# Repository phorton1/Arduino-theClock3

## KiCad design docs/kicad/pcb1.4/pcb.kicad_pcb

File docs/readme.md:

# theClock3 - Accurate Electromagnetic Wooden Geared Clock

**Home** --
**[Design](design.md)** --
**[Plan](plan.md)** --
**[Wood](wood.md)** --
**[Coils](coils.md)** --
**[Electronics](electronics.md)** --
**[Firmware](firmware.md)** --
**[Assemble](assemble.md)** --
**[Build](build.md)** --
**[Tuning](tuning.md)** --
**[UI](ui.md)** --
**[Software](software.md)** --
**[Troubles](troubles.md)** --
**[Notes](notes.md)**

This clock uses wooden gears and a simple electromagnetically driven pendulum
with the goal of keeping accurate time.

It uses an an **electromagnet** and **permanent magnet** to provide pulses of energy
to the pendulum to keep it moving, an **angle sensor** to detect the position
of the pendulum, and a **magnetic spring** to to speed up, or slow down, the pendulum.

It uses a specially designed **cam driven pawl** mechanism to
reliably convert the motion of the pendulum in each direction
to the rotation of the **seconds wheel** and **gear train**.

It has a computer (an [**ESP32**](https://en.wikipedia.org/wiki/ESP32)) in it,
with a *Real Time Clock* (**RTC**) that is fairly accurate (to within about 1 second per day).
Furthermore the computer can connect to the internet to use Network Time Protocol
([**NTP**](https://en.wikipedia.org/wiki/Network_Time_Protocol))
to synchronize it's RTC within a few milliseconds of the *correct* international
**standard time**.

Roughly stated, the goal of this project is to produce a **wooden geared clock**
that will be accurate to within one second per day, or, when connected to the
internet, within one second at any given time over it's working lifetime.

This documentation is mostly geared towards makers who might like to build
one of these clocks. Though it is not a trivial task, this repository should
contain all of the information needed for you to build one.

## Documentation Outline

If you have received one of these clocks as a gift, please see the
**[Quick Start Guide](QuickStartGuide.pdf)** and the
**[User Interface](ui.md)** page for information on how to unpack,
setup, start, and use your clock.

The following pages of documentation are intended to as a *tutorial* for
a **maker** who is *building* a clock, and describes the step-by-step
process of constructing the clock and getting it running:

- **[Design](design.md)** - An overview of the **requirements** and **design** of the clock
- **[Plan](plan.md)** - A *plan* for **building** the clock, and the **BOM** (Bill of Materials)
- **[Wood](wood.md)** - **Laser Cutting** the wood and building the *Frame*, *Face*, and gluing the *Gears* together
- **[Coils](coils.md)** - **Winding** the *electromagnet coils*
- **[Electronics](electronics.md)** - Creating the custom **PCB** (printed circuit board), **Cables**, and **Connectors**
- **[Firmware](firmware.md)** - Compiling and installing the **Firmware** and doing a  **hardware test** of the electronics
- **[Assemble](assemble.md)** - Build the **sub-assemblies** of the clock, including **cutting the tubes** and assembling the **Gears, Pendulum,** and **Box**
- **[Build](build.md)** - **Final Build** of the clock, bringing all the *sub-assemblies* together into the finished *Clock*
- **[Tuning](tuning.md)** - Describes the process of getting the clock to **run accurately**

The remaining pages are considered **reference** materials for more
deeply understanding the clock and it's software:

- **[User Interface](ui.md)** - A detailed guide to the **User Interface** of the clock, including the *Buttons and LEDs*, and connecting to *WiFi* to use the *WebUI* and *Telnet*
- **[Software](software.md)** - A deeper look the **Software** of the clock, including an *Overview* of the functionality and a description of all of the *Parameters* for the clock
- **[Trouble Shooting](troubles.md)** - Some common potential **problems** and possible **solutions**
- **[Notes](notes.md)** - Other Notes and information about the clock

## Files Available in this repository

This clock was *designed* using the **Fusion 360** CAD program and
the [**KiCAD**](https://www.kicad.org/) schematic and PCB design program.
The main outputs from Fusion 360 are the **DXF Files** (drawings) used to laser
cut the wood, and the **STL Files** (3D models) used to 3D print the plastic parts.

The clock was *implemented* by using the **Lightburn** laser CNC machine
control program to cut the wood from the Fusion DXF files using my
[**20mm CNC machine**](https://github.com/phorton1/Arduino-esp32_cnc20mm),
and the **Prusa Slicer** and **OctoPrint** to slice the Fusion STL files and send
them to my **Prusa MK3S 3d printer** to make the plastic parts.

The PCB (printed circuit board) is almost it's own sub-project.
The outputs from *KiCad* include the basic **schematic**, and
the **Gerber** and **Excellon** files used to make the PCB.
The program [**FlatCAM**](https://bitbucket.org/jpcgt/flatcam/downloads/)
was used to generate the GCODE files from those files for running my
[**cnc3018**](https://github.com/phorton1/Arduino-esp32_cnc3018)
to **mill, epoxy coat, drill, and cut out** the PCB (printed circuit board.

The following sub-folders and their children can be found within this 'docs' folder

- [**fusion**](https://github.com/phorton1/Arduino-theClock3/tree/master/docs/fusion) -
   contains the main *Fusion 360* design **clock3.2.f3z**, as well as a few
   other files that support the design, including a CSV file containing parameters for
   the design, and a couple of **pyjoints** animations (which make use of the
   Fusion 360 [pyJoints Animation Plugin](https://github.com/phorton1/fusionAddIns-pyJoints)
   I wrote) that allowed me to visually test the design before implementing it.
  - [**dxf**](https://github.com/phorton1/Arduino-theClock3/tree/master/docs/fusion/dxf) -
    contains all of the DXF files used with **Lightburn** to laser cut the wooden parts
  - [**stl**](https://github.com/phorton1/Arduino-theClock3/tree/master/docs/fusion/stl) -
    contains STL files of all the plastic parts that I 3D printed
- [**kicad/pcb3.1**](https://github.com/phorton1/Arduino-theClock3/tree/master/docs/kicad/pcb3.1) -
  contains the **kiCAD** project, electronics schematics, and PCB design files
  - [**plot**](https://github.com/phorton1/Arduino-theClock3/tree/master/docs/kicad/pcb3.1/plot) -
    contains the Gerber/Excelon files output from kiCAD, along with the
    **FlatCAM** project used to produce the gcode files for milling, epoxy coating,
	drilling, and cutting out the PCB
    - [**gcode**](https://github.com/phorton1/Arduino-theClock3/tree/master/docs/kicad/pcb3.1/plot/gcode) -
	contains the final output gcode files for the PCB
- [**lightburn**](https://github.com/phorton1/Arduino-theClock3/tree/master/docs/lightburn) -
   contains **LBRN2** Lightburn files that contain all of
   the wooden parts to be laser cut, as well as individual files to cut
   the different thicknesses or types of wood
- [**prusa**](https://github.com/phorton1/Arduino-theClock3/tree/master/docs/prusa) -
   contains the Prusa **3mf** projects for the plastic parts I sliced
  - [**gcode**](https://github.com/phorton1/Arduino-theClock3/tree/master/docs/prusa/gcode) -
    contains the final output *Prusa MK3s* gcode files that I used to
    3D print the plastic parts

If you are a **maker** you do not necessarily need to mill your own PCB as I did.
You can implement this simple circuit using **perfboard**, or can use the
kicad files to (fairly quickly) design your own PCB to be created
from your favorite PCB supplier.   I simply choose to mill my own PCB's
because I don't live in a good place for shipments and am too impatient
to wait weeks (or months) to get a PCB.  You might be able to get one
from China in a few days, but it takes much longer for me where I live.

Another example is that you don't **need** to laser cut the wooden parts.
It should be possible to use a small CNC machine (3018) to mill the gears, and
either a slightly larger CNC machine to mill the frame parts, or they could
even be cut using templates and a jigsaw or scroll saw.

**HOW YOU BUILD IT IS UP TO YOU !!**

The reason I provide so much information in these pages (rather than just the bare minimum)
is specifically to allow some flexibility for your design/build workflow.
When I went to make my first wooden (and especially laser cut) clock, I could not find
any complete designs that I could build.  So I am hoping that the info here will
provide you both with the materials you need, and perhaps the impetus, to build
one of your own!

## Credits

This project directly relies upon the public open source Arduino development system,
the Espressif ESP32 online documentation and additions to the Arduino IDE, as
well as a number open source Arduino libraries

I would like to thank the countless individuals who have contributed to making these
development tools, source codes, and documentation available for free public use, including,
but not limited to:

- [KiCad](https://www.kicad.org/)
- [FlatCAM](https://bitbucket.org/jpcgt/flatcam/downloads/) by **Juan Pablo Caram**
- [Arduino IDE and Libraries](https://www.arduino.cc/)
- [Espressif Systems](https://www.espressif.com/en/products/socs/esp32)
- [Adafruit NeoPixel Library](https://github.com/adafruit/Adafruit_NeoPixel)
- [AS5600 Library](https://github.com/RobTillaart/AS5600) by **Rob Tillaart**

## License

This program, project, and repository is free software: you can redistribute it and/or modify
it under the terms of the GNU General Public License Version 3 as published by
the Free Software Foundation.

These materials are distributed in the hope that they will be useful,
but WITHOUT ANY WARRANTY; without even the implied warranty of
MERCHANTABILITY or FITNESS FOR ANY PARTICULAR PURPOSE.  See the
GNU General Public License for more details.

Please see [LICENSE.TXT](../LICENSE.TXT) for more information.

## Please Also See

This project directly or indirectly brings together a number of other projects of mine.
It supersedes my previous clock projects, [**theClocks 1&2**](https://github.com/phorton1/Arduino-theClock),
and makes direct use of my
[**MyIOT**](https://github.com/phorton1/Arduino-libraries-myIOT)
("my internet of things*) repository, which provides a generalized approach to building parameter
driven ESP32 devices that include a Web UI, as the basis for the software.

Another project that also make user of the *myIOT* repository is the
[**Bilge Alarm**](https://github.com/phorton1/Arduino-bilgeAlarm)
that I built for my boat.

The PCB (printed circuit board) was **milled** using the
[**cnc3018**](https://github.com/phorton1/Arduino-esp32_cnc3018) CNC
machine that I built, and the wooden parts were cut using the laser configuration of the larger
[**20mm CNC machine**](https://github.com/phorton1/Arduino-esp32_cnc20mm) that I subsequently built.
Both of those projects depend on my port of the
[**FluidNC**](https://github.com/phorton1/Arduino-libraries-FluidNC)
ESP32 based CNC controller firmware, and include my
[**FluidNC UI**](https://github.com/phorton1/Arduino-libraries-FluidNC_UI)
(touchscreen user interface) and
[**other extensions**](https://github.com/phorton1/Arduino-libraries-FluidNC_Extensions)
that I added to the FluidNC library.

There is also a quick and dirty
[**Coil Winding Machine**](https://github.com/phorton1/Arduino-CoilWindingMachine)
project repository for the machine I made to wind the coils for these clocks and
a [Fusion 360 Plugin](https://github.com/phorton1/fusionAddIns-pyJoints)
that I created which allowed me to do animations of the clock to visually see how the
mechanism might work before actually building it.

I hope you will take a few minutes to check out some of these other pages too!!

**Next:** A [**Design Overview**](design.md) of the clock ...

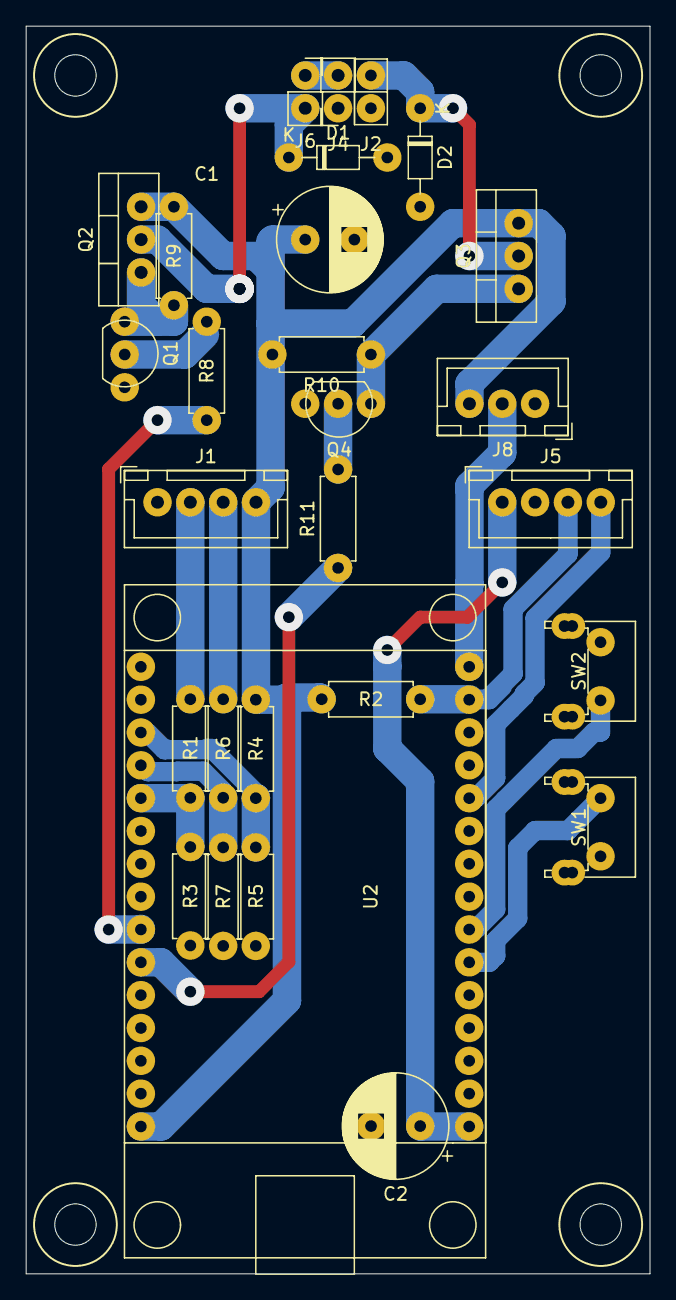
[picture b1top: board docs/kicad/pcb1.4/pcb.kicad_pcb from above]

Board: 2 copper layers, 48.3 x 96.5 mm, 28 parts (0 on the bottom side), 22 nets.

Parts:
C1: 330uf; CP_my100uf
C2: 100 uf; CP_my100uf
D1, D2: 1N4741; myZenerDiode
J1: power; myJSTx04
J2: coil3; myPinSocket_1x02
J4: coil1; myPinSocket_1x02
J5: Sensor; myJSTx04
J6: coil2; myPinSocket_1x02
J8: leds; myJSTx03
Q1, Q4: BC548; myTransistor
Q2, Q3: IRF9540N; myThreeLegged
R1, R2, R3, R4, R5, R6, R7, R8, R9, R10, R11: 10K; myResistor
SW1, SW2: SW; myButtonAngled
U2: ESP32_DEV_0; myESP32DEV0

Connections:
+3V3: C2.1, J5.1, U2.30
+5V: C1.1, J1.4, J8.3, Q2.3, Q3.3, R2.1, R4.2, R9.2, R10.2, U2.1
COIL1+: D1.1, J6.2, Q2.2
COIL2+: D2.1, J2.2, Q3.2
GND: C1.2, C2.2, D1.2, D2.2, J1.1, J2.1, J4.1, J5.2, J8.1, Q1.3, Q4.3, R3.2, R5.2, R7.2, SW1.2, SW2.1, U2.2, U2.29
LEDS: J8.2, U2.16
unnamed: J4.2, J6.1
unnamed: Q1.1, Q2.1, R9.1
unnamed: Q1.2, R8.2
unnamed: Q3.1, Q4.1, R10.1
unnamed: Q4.2, R11.2
PWM1: R8.1, U2.7
PWM2: R11.1, U2.6
S5V: R4.1, R5.1, U2.13
SBAT: R1.1, R3.1, U2.11
SBUS: R6.1, R7.1, U2.12
SCL: J5.3, R2.2, U2.17
SDA: J5.4, U2.20
SW1: SW1.1, U2.25
SW2: SW2.2, U2.24
VBAT: J1.2, R1.2
VBUS: J1.3, R6.2

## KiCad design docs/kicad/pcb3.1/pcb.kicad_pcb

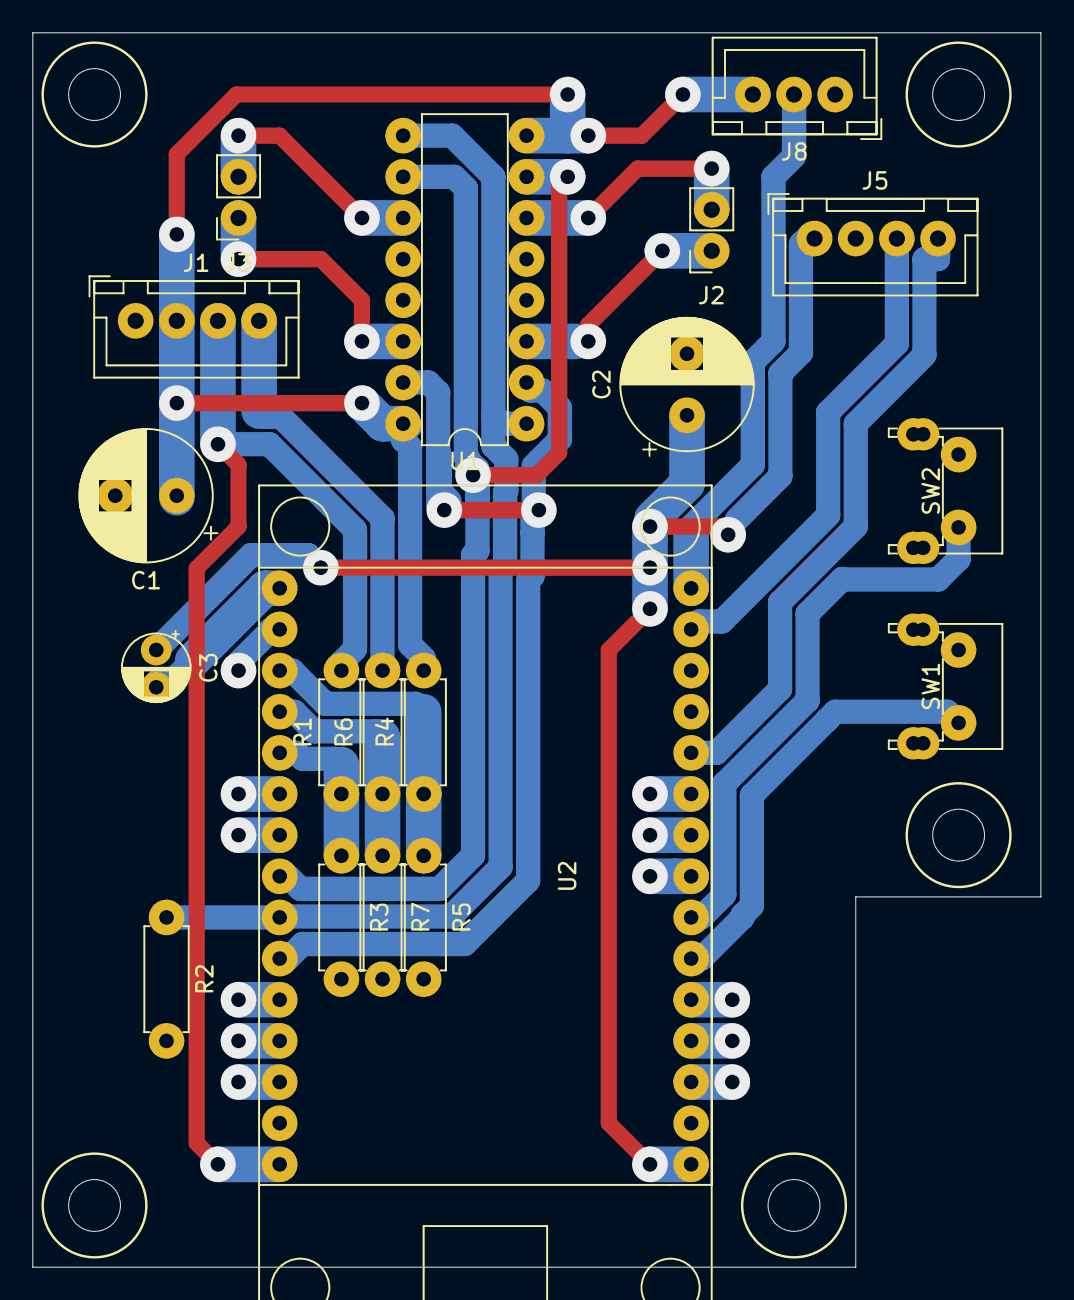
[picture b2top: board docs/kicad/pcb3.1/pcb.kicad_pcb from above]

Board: 2 copper layers, 62.2 x 76.2 mm, 19 parts (0 on the bottom side), 21 nets.

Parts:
C1: 100uf; CP_my100uf
C2: 470uf; CP_my100uf
C3: 10uf; CP_my10uf
J1: power; myJSTx04
J2: coil1; myPinSocket_1x02
J3: coil2; myPinSocket_1x02
J5: Sensor; myJSTx04
J8: leds; myJSTx03
R1, R2, R3, R4, R5, R6, R7: 10K; myResistor
SW1, SW2: SW; myButtonAngled
U1: L293D; myDip16
U2: ESP32_DEV_0; myESP32DEV0

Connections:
+3V3: C2.1, C3.1, J5.1, U2.30
+5V: C1.1, J1.2, J8.3, R4.2, U1.8, U1.16
EN: R2.1, U1.1, U1.9, U2.7
GND: C1.2, C2.2, J1.1, J5.2, J8.1, R2.2, R3.2, R5.2, R7.2, SW1.1, SW2.1, U1.4, U1.5, U1.12, U1.13, U2.2, U2.29
I1: U1.2, U1.15, U2.6
I2: U1.7, U1.10, U2.8
LEDS: J8.2, U2.16
unnamed: C3.2, U2.15
OA1: J2.1, U1.3
OA2: J2.2, U1.6
OB1: J3.1, U1.14
OB2: J3.2, U1.11
S5V: R4.1, R5.1, U2.13
SBAT: R6.1, R7.1, U2.12
SBUS: R1.1, R3.1, U2.11
SCL: J5.3, U2.17
SDA: J5.4, U2.20
SW1: SW1.2, U2.25
SW2: SW2.2, U2.24
VBAT: J1.4, R6.2
VBUS: J1.3, R1.2, U2.1

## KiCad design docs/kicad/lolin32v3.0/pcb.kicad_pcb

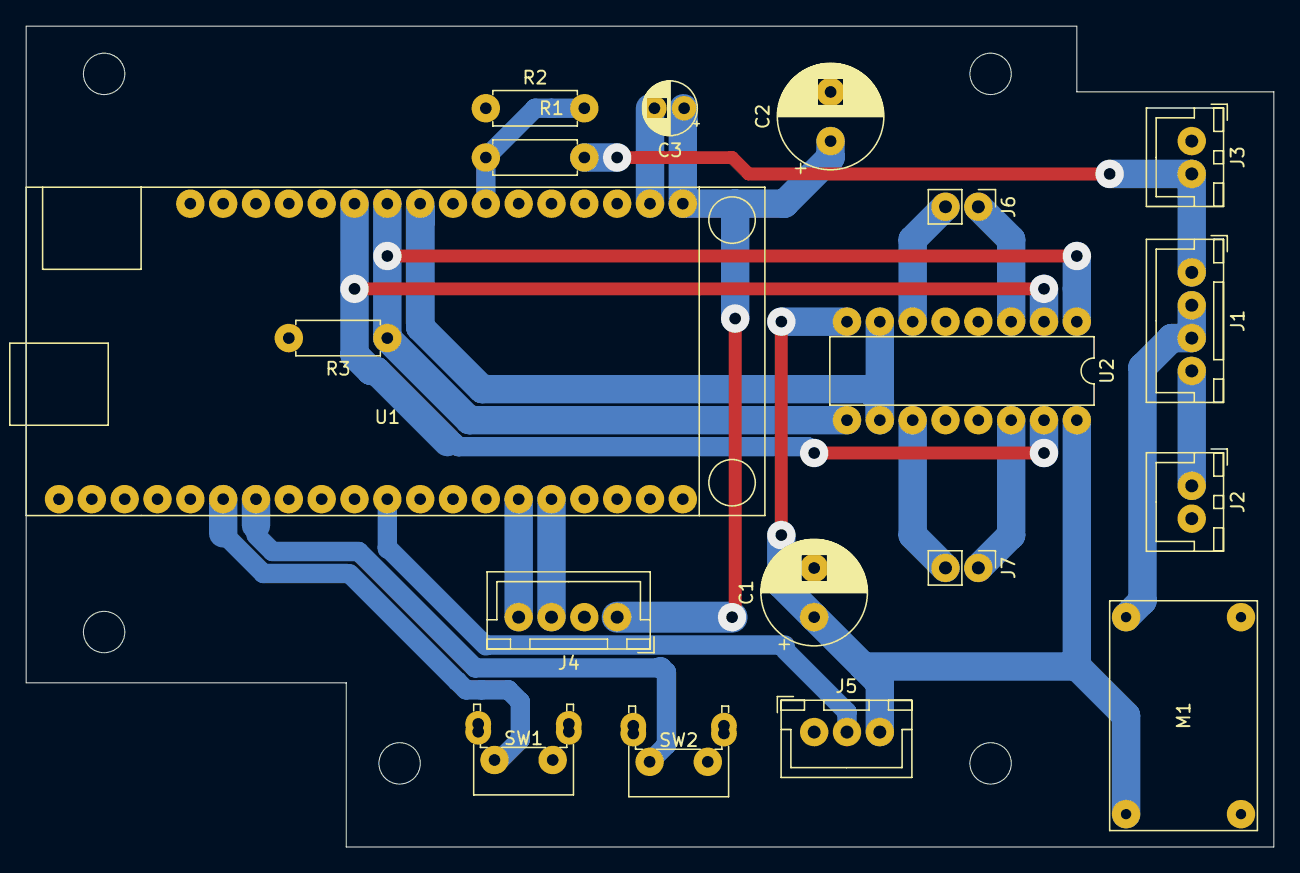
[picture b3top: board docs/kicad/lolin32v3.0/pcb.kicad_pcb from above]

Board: 2 copper layers, 96.5 x 63.5 mm, 18 parts (0 on the bottom side), 20 nets.

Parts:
C1, C2: 100uf; CP_my100uf
C3: 10uf; CP_my10uf
J1: power; myJSTx04
J2: battery; myJSTx02
J3: BATT; myJSTx02
J4: Sens1; myJSTx04
J5: leds; myJSTx03
J6: coil1; myPinHeader_1x02
J7: coil2; myPinHeader_1x02
M1: BUCK01; myMini360BuckConverter
R1, R2: 47K; myResistor
R3: 10K; myResistor
SW1, SW2: SW; right_angle_button
U1: LOLIN32; myLolin32
U2: L293D; myDip16

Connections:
+3V3: C2.1, C3.1, J4.1, U1.21
+5V: C1.1, J5.3, M1.3, U2.8, U2.16
BAT+: J1.1, J3.2, R1.2
BAT_SENSE: R1.1, R2.2, U1.27
EN: R3.1, U1.30, U2.1, U2.9
GND: C1.2, C2.2, J2.2, J3.1, J4.2, J5.1, M1.1, M1.2, R2.1, R3.2, SW1.1, SW2.1, U1.3, U1.13, U1.14, U1.20, U1.36, U2.4, U2.5, U2.12, U2.13
I1: U1.31, U2.2, U2.15
I2: U1.29, U2.7, U2.10
LEDS: J5.2, U1.11
unnamed: C3.2, U1.22
unnamed: J1.2, J1.3, M1.4
unnamed: J1.4, J2.1
OA1: J6.1, U2.3
OA2: J6.2, U2.6
OB1: J7.1, U2.14
OB2: J7.2, U2.11
SCL: J4.3, U1.16
SDA: J4.4, U1.15
SW1: SW1.2, U1.6
SW2: SW2.2, U1.7

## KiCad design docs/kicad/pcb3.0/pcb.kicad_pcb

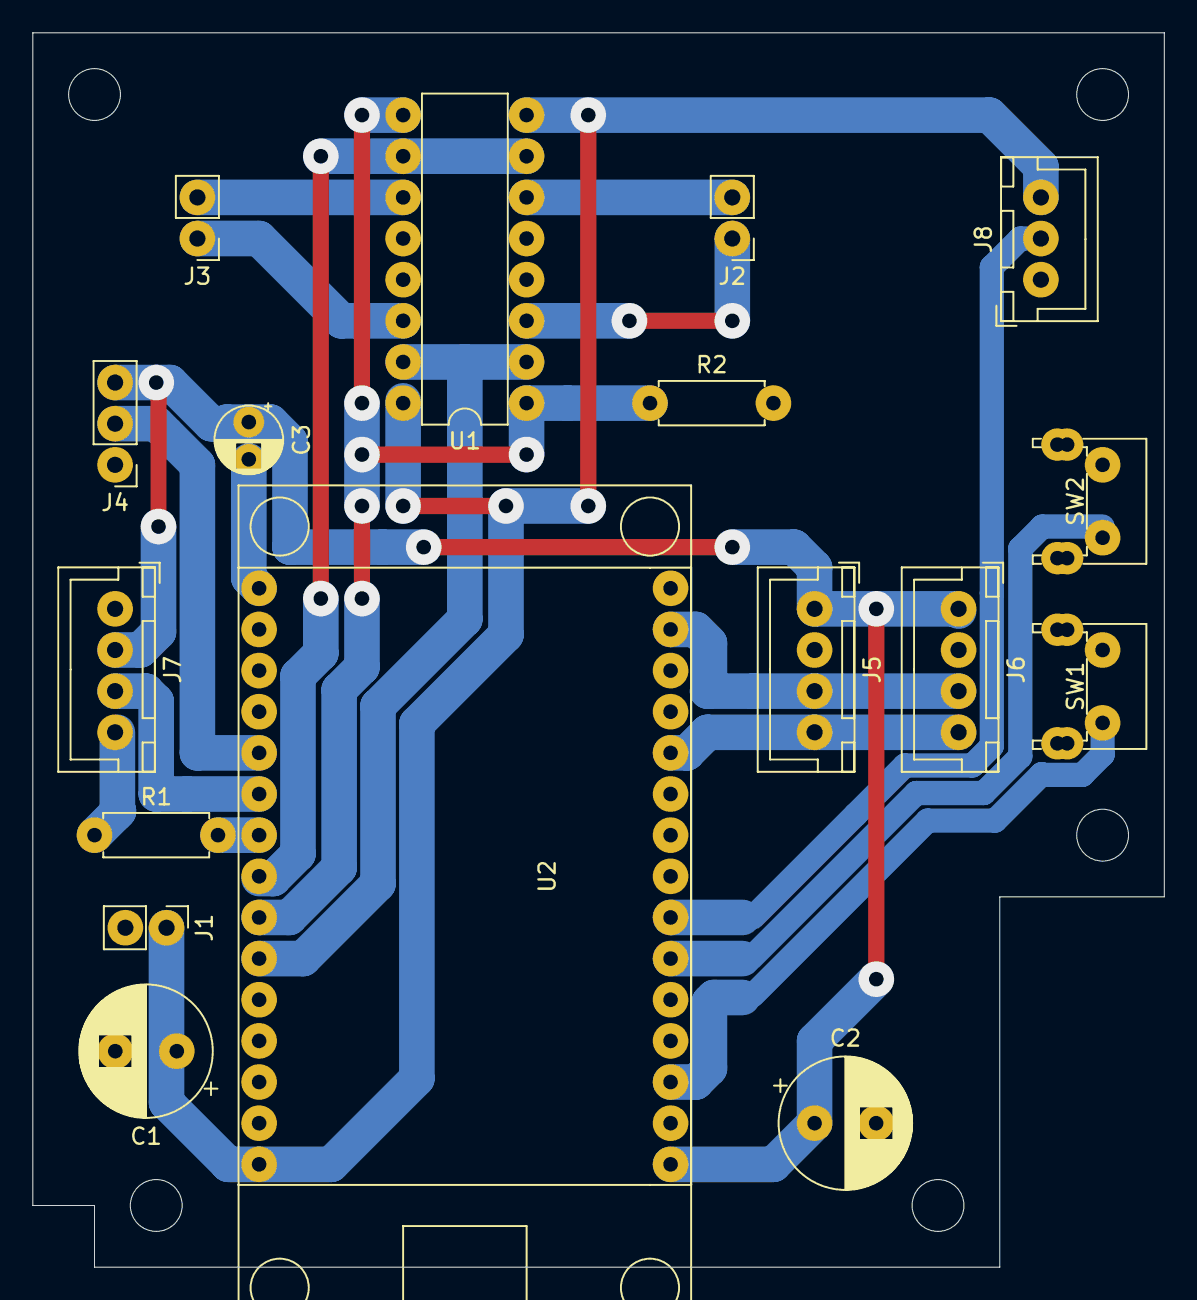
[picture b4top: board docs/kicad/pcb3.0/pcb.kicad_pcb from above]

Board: 2 copper layers, 69.8 x 76.2 mm, 17 parts (0 on the bottom side), 20 nets.

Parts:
C1, C2: 100uf; CP_my100uf
C3: 10uf; CP_my10uf
J1: power; myPinHeader_1x02
J2: coil1; myPinHeader_1x02
J3: coil2; myPinHeader_1x02
J4: hall; myPinHeader_1x03
J5: Sens1; myJSTx04
J6: Sens2; myJSTx04
J7: Opto; myJSTx04
J8: leds; myJSTx03
R1: 220; myResistor
R2: 10K; myResistor
SW1, SW2: SW; right_angle_button
U1: L293D; myDip16
U2: ESP32_DEV_0; myESP32DEV0

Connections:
+3V3: C2.1, C3.1, J4.3, J5.1, J6.1, J7.2, U2.30
+5V: C1.1, J1.1, J8.3, U1.8, U1.16, U2.1
EN: R2.1, U1.1, U1.9, U2.7
GND: C1.2, C2.2, J1.2, J4.1, J5.2, J6.2, J7.1, J8.1, R2.2, SW1.1, SW2.1, U1.4, U1.5, U1.12, U1.13, U2.2, U2.29
I1: U1.2, U1.15, U2.6
I2: U1.7, U1.10, U2.8
LEDS: J8.2, U2.24
unnamed: C3.2, U2.15
unnamed: J7.4, R1.1
OA1: J2.1, U1.3
OA2: J2.2, U1.6
OB1: J3.1, U1.14
OB2: J3.2, U1.11
SCK: J7.3, U2.10
SCL: J5.3, J6.3, U2.17
SDA: J5.4, J6.4, U2.20
SDIO: R1.2, U2.9
SW1: SW1.2, U2.28
SW2: SW2.2, U2.25
hall: J4.2, U2.11

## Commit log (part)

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2023-03-16 copy files from theClock/pcb1.1, rename, and check in
2023-03-17 initial v3 circuit board, pin assigments in code TODO: code in general
2023-03-21 add 'data' directory
2023-03-21 correct 5165 to 5155!! bearing
2023-03-21 build wood and plastic
2023-03-21 revert to 5165 bearing
2023-03-22 changed to 2.6 screw3_tight_wood, updated drawings, got rid of most lightburn for eas of maintenance
2023-03-25 change 3.1 to 3.0 and generate flatcam stuff
2023-03-27 build thinner v3.0
2023-03-27 begin work on code for v3
2023-03-30 initial commit of swing degree PID controller
2023-03-30 fixed magnet sixe in pendulum
2023-03-30 various minor physical changes
2023-03-30 added alternate arm2 and pawl2
2023-03-30 remove HALL, cleanup, initial STATS
2023-03-31 initial working checkin (BEFORE SOLVING BASIC FREQUENCY ISSUE)
2023-03-31 BETTER ALGORITHM - KEEPS TIME AND ANGLE PRETTY WELL!
2023-04-02 constants and colors only
2023-04-02 blah blah blah
2023-04-03 sanity checkin - trying to run down AS5600 error - changed startup logic, parameterized much additional stuff, still just skips bad as5600 readings ... sigh
2023-04-06 change sync message display (only)
2023-04-10 2ND PID CONTROLLER - NEW ALGORITHM - NO "PULLS" - WORKS GOOD
2023-04-10 refine constants; design and print magnet_holder; prep for startClockSynchronized
2023-04-11 rework LEDS in prep for startClockSynchronized()
2023-04-12 fighting with detailed synchronization and readAngle() vs showPixels()
2023-04-13 added PIXEL_MODE and LED_BRIGHTNESS; had problem with loop() static uint32_t!!! messed with IRAM_ATTR; solution? --> made many vars volatile;
2023-04-14 move long comments from code to readme
2023-04-15 FOUND THE MEMORY BUG! - got rid of volatiles - fixed timeAddMS *secs-- and onSyncRTC sign problem - made clearStats() really start over
2023-04-15 defaults, LOG, and wifi_off BLUE_LED only
2023-04-16 minor changes (prep for big myIOT rewrite?)
2023-04-16 fixed compiler warnings and one bug with this_p = cur_cycle
2023-04-16 change cur_cycle to int32_t; indentation and comments
2023-04-16 factor code - prep for doButtons()
2023-04-16 implement buttons; test default values;
2023-04-17 added Wifi checks to onSyncRTC
2023-04-17 implemented PIXEL_TIME_MODE
2023-04-17 fixed PIXEL_MODE_TIME time intervals and added m_start_sync==MY_LED_WHITE
2023-04-18 added button support for PIXEL_MODE_TIME and changed colors again
2023-04-19 CREATED V1.3 as clock 1.1 with V3 sensor and software
2023-04-21 turn off V1.3 define
2023-04-21 added adjustable ranges for DIAG _cycle_range and _error_range pixels
2023-04-22 separated V1 PINS from BEHAVIOR so I could build LOLIN32 with correct pins, but V1 behavior
2023-04-22 test change for github auth
2023-04-22 nuther github auth test
2023-04-23 LOLIN32 pcb - changed voltage divider resistors
2023-04-23 Added WITH_VOLT_CHECK define, turns on PIN_VOLT_CHECK and parameters VOLT_VALUE, VOLT_INTERVAL, and VOLT_CALIB
2023-04-23 Retry initing AS5600 a few times if it fails
2023-04-23 made ID_RUNNING memory only and changed START_SYNC to a real boolean parameter
2023-04-23 made global as5600_connected and changed getAS5600Angle() to return zero_angle if not connected and always update_direction
2023-04-23 basic implementation (and stats) for LOW_POWER_MODE
2023-04-23 moved REVERSE_PIXELS up - checked in with LOLIN32 test circuit defines
2023-04-25 added lolin32 pcb & step; started 5VUPS schematic
2023-04-25 made V1.3 defaults official - checked in as V3.1
2023-04-28 added 3.1 pcb, dxfs, prepare to build
2023-05-01 update constants. clear ang_error on sync done
2023-05-01 rebuild normal ESP32_dev0
2023-05-03 yet another tuning of clock3
2023-05-08 latest constants for 3.1 clock
2023-05-09 finish wood build
2023-05-12 diddle params again, add BOM, and washer_x8.gcode
2023-05-21 various extra files generated while building 3 x v3.2 clocks
2023-05-21 upgrade to version 3.2 and default correct clock3 pins
2023-05-27 re-implemented START_SYNC to use ms before 0 to start (was ms after 59 previously)
2023-05-27 temporary 'alternate arms' build
2023-05-31 comment only
2023-06-01 FINALISH BUILD THREE CLOCKS - lots of changes changed startAS5600 to flash all LEDs upon failure, and for CLOCK_STATE led to flash red in that case. changed setZeroAngle() to retry upto 5 times 45 to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
2023-06-07 updated to new captive.html
2023-06-07 changed medium press to CYAN for better distinction
2023-06-08 added QuickStartGuide.docx, removed versioned output files
2023-06-09 2023-06-08 Shipped Quick Start Guide
2023-06-09 push to test videos
2023-06-12 spell_checked readme.md
2023-06-14 documentation WIP - add Build and Firmware pages; cleanup lightburn and prusa materials
2023-06-16 documentation WIP - changed "rider" to "bridge" and "frame main" to "frame middle"
2023-06-16 Docs - add link(s) to new Arduino-CoilWindingMachine repository
2023-06-17 Docs - renamed fusion tool parts to "Left" and "Right", finished "Coils" page and renamed "Plastic" to "Box"
2023-06-19 documentation WIP thru "software.md"
2023-06-20 documentation WIP - sorta finished other.md
2023-06-21 updated pcb3.3 (no plots, flatcam, or gcode)
2023-06-21 changed v3.3 defaults for SERIES coils with mosfet board. Implemented negative start_delay AFTER zero. Set default RESSTART_MIILLIS=0
2023-06-24 Rework PCB3.3, import it into fusion, more documentation WIP
2023-06-24 fixed bad bridge DXF file
2023-06-24 fusion selection sets for USB mount and quick UPS mount for box
2023-06-25 got rid of fusion internal USB_UPS, added external USB_UPS box
2023-06-25 fusion usb_usp forgot an extrusion
2023-06-26 update documentation to new pcb3.3 MOSFET PCB
2023-06-26 docs electronics continued ..
2023-06-27 document WIP - assembly.md
2023-06-28 updated/added pics, added YouTube WindingCoils video
2023-06-29 docs - added Ticking YouTube video, Build (ticking) Animation, and more images to Other page
2023-06-29 doc - added assem-top_tube.gif, spell checked thru assem
2023-07-02 docs - added FinalBuildMontage youtube video, renamed pages and images
2023-07-02 github does not like <style> elements in MD files
2023-07-02 doc typos and minor corrections
2023-07-04 started docs Tuning WIP
2023-07-04 docs - Finished "Tuning" page
2023-07-04 docs - shrink build-gears.gif image
2023-07-05 cleaned up PARAM DEFINES; added PARAMS to ui.md (WIP); updated javascript to use Tooltips
2023-07-06 doc WIP - ui.md LEDs mostly
2023-07-06 test tables on github
2023-07-06 docs ui fix startup LED image
2023-07-06 docs misc
2023-07-06 Unified section number schemes ## A,B,C ... and ### 1,2,3....
2023-07-07 docs - added software-connectWebUI and anchor links
2023-07-08 doc WIP - UI continued
2023-07-08 docs - rename software to firmware and break software.md out of ui.md
2023-07-08 docs - fix broken links
2023-07-08 docs - start Notes page
2023-07-08 docs-notes - added optional 2nd USB connector and UPS Power Supply
2023-07-08 docs - finished notes page
2023-07-09 docs - initial public push
2023-07-09 doc - typos
2023-07-10 doc typos
2023-07-10 doc - make USB_UPS box bigger
2023-07-10 cleaned up LOW_POWER stats
2023-07-10 changed DEFAULT_RUNNING_ERROR to 4 degrees, added PID comments for v3.2 built #3/3, fix sminor doc typos
2023-09-13 update preferences.txt to new port
2023-10-20 comments only
2023-11-02 nuther try
2023-11-02 one more try
2023-11-02 fix broken links across all repos with introduction of base-apps-gitUI::repoDocs.pm
2024-01-07 IMPLEMENT CLOCK 1.4 with new PCB and 2nd Spring Coil - clean up defines, etc.
2024-01-10 added CLEAR_ERRORS command/id/button etc
2024-02-03 refine clock 1.4 to USE_LEFT angle for m_angle_pid for consistent spring behavior
2024-02-11 changed 1.04 to simple ALL-ON or ALL-OFF spring algorithm with new tuning
2024-03-01 rebuild clock3
2024-03-01 remove data folder for change to submodule
2024-03-01 made 'data' directory into submodule of myIOT/data_master
2024-07-19 submodule(data) auto_commit(9478759f) addl iotCommon.js submodule changes for control and disabled_classses
2024-09-08 comments only RETUNED PID for clock3.3
2024-09-21 submodule(data) auto_commit(83767cf1) Added a Widget tab to the main myIOT webpage; added jqplot CSS and JS files; wrote iotPlot.js prototype of charting within a "widget" - see fridgeController chec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
2024-09-22 submodule(data) auto_commit(e76456cf) iotPlot.js - minor change to Fix Zooming; otherwise "comments only"
2024-09-25 refined myIOT plotter with LEGENDS and using device specific PLOT_TYPES if available; theClock3 implementation of PLOT_CYCLES and PLOT_WAVES
2024-09-25 submodule(data) auto_commit(331f60b7) refined myIOT plotter with LEGENDS and using device specific PLOT_TYPES if available; theClock3 implementation of PLOT_CYCLES and PLOT_WAVES
2024-09-25 submodule(data) auto_commit(18ec6f60) iotPlot.js - missing ctx.lineWidth = 1; for plot itself
2024-09-26 submodule(data) auto_commit(68039dc2) prep for bilgeAlarm bar chart widget - reworked myIOTDataLog to send records from back of file until dt stamp is met, which required myIOTWebServer to use HTTP 1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
2024-09-29 submodule(data) auto_commit(416ed000) added prototype bilgeAlarm jqPlot Widget using added "alt_data_format" and custom chart_header and chart_data code in onCustomLink(). modified myIOT/data index.h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
2024-10-01 submodule(data) auto_commit(2407a228) added global DEGREE_TYPE and VALUE_STYLE_TEMPERATURE, supprted in webUI, dataLog, and Charts
2024-10-07 submodule(data) auto_commit(f3e2065d) reduce size of WS status fields in index.html
2024-10-10 submodule(data) auto_commit(b622c3ba) Use regular javascript alert instead of myAlert and hide progress on upload_error
2024-10-19 submodule(data) auto_commit(c0e7ba5a) add better resizing to iotChart.js
2024-10-25 submodule(data) auto_commit(fdbad871) fix myIOTServer with new chart stuff (pass uuids, caching, etc)
2024-11-07 refork NMEA2000 libraries; cleanup FluidNC_Extensions::mesh.cpp() and cnc3018.h CNC_MACHINE, UI_WITH_MESH and USE_LARGE Mesh defines and compile messages - turning off default definition of UI_WITH_M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
2025-12-15 submodule(data) auto_commit(b649fc3a) iotChart.js - added scheme for setting device specific series colors
2025-12-18 submodule(data) auto_commit(1adaeb45) reworked iotChart.js incremental update scheme starting with Arduino-boat-drainPump
2025-12-18 submodule(data) auto_commit(1efc7b72) rework iotChart.js::determineNumberTicks() starting with drain_pump
2025-12-18 submodule(data) auto_commit(78894e93) change onChartResize() to use create_chart() instead of built in jqplot.replot()
2025-12-18 submodule(data) auto_commit(40916b0c) separate iotChart.js doChart() as init only method from onXXX() UI methods - yet another rework of iotChart.js and myIOTDataLog starting with fridgeController
2025-12-18 submodule(data) auto_commit(a4e2ed81) change chart.html and iotChart.js to use and remove style "degree_hidden" for devices that chart things with degrees
2025-12-18 submodule(data) auto_commit(a9754dbc) fixed renamed control _degree_type
2025-12-18 submodule(data) auto_commit(03555741) fix malformed chart.html <select id='_chart_period'> text
2025-12-19 submodule(data) auto_commit(253976a9) more changes to iotChart.js starting with tempController so at least refresh works *well* if no zooming involved
2025-12-19 commit parents
2025-12-20 submodule(data) auto_commit(eccd1fcc) iotChart.js - added save/restore of series visibility and refactored code
2025-12-31 submodule(data) auto_commit(2a8db875) add degree_type to myIOT chart_header for use in initializing iotChart.js
2026-03-04 submodule(data) auto_commit(75bcbcb5) iotChart.js - added smaller (UINT8, CENTIGRADE8, UINT8x10) iotDataLog LOG_TYPES and updated client ctors
2026-03-04 submodule(data) auto_commit(d6f02205) added myIotTempSensor "raw" accessors & used to shrink fridgeController.dataLog file size; got rid of FAKE_COMPRESSOR
2026-03-04 got rid of dubious ability to turn myIOT WIFI off and on
2026-03-07 submodule(data) auto_commit(5dbe3136) Save chart visibility and zorders in locsl storage
2026-04-04 submodule(data) auto_commit(a0279fca) New iotChart tooltips and dataLog record maintenance feature.

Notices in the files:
docs/readme.md:
License:
This program, project, and repository is free software: you can redistribute it and/or modify
it under the terms of the GNU General Public License Version 3 as published by
the Free Software Foundation.
These materials are distributed in the hope that they will be useful,
but WITHOUT ANY WARRANTY; without even the implied warranty of
MERCHANTABILITY or FITNESS FOR ANY PARTICULAR PURPOSE.  See the
GNU General Public License for more details.
Please see [LICENSE.TXT](../LICENSE.TXT) for more information.
